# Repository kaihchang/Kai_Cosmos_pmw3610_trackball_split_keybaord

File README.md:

# Kai Cosmos 40, a ZMK split keyboard with pmw3610 trackball

👉 ZMK firmware |
[Dongle-less](https://github.com/kaihchang/zmk-config-kai-cosmos) |
[With Dongle](https://github.com/kaihchang/zmk-config-kai-cosmos-dongle)

Design is mostly created using [rianadon's Cosmos Keyboard Configurator](https://github.com/rianadon/Cosmos-Keyboards). Highly recommend! It's a godsend.

What I did:
1. Scan my own hands with the tools Cosmos Keyboard Configurator provided and my phone's camera.
2. Add a 34mm trackball with [Skree ZMK pmw3610 board](https://github.com/siderakb/pmw3610-pcb) to the right side, which will also be ZMK's main side.
3. Download the models and edit in Blender and Fusion to smooth out the corners.
4. Using the microcontroller template from Cosmos Keyboard Configurator to draw out PCB in Kicad.
5. Implement [badjeff's zmk-pmw3610-driver](https://github.com/badjeff/zmk-pmw3610-driver/tree/main) with some official ZMK settings. Documentations aren't really clear, I recommend searching certain attributes and copying from public repos on Github.
6. Solder, test, change keymap, rinse and repeat.

Things for further improvements:
1. Reset button should be set under MCU holder PCB for easier access.
2. Should have cutouts under MCUs to make built-in LEDs more visible.
3. Should have copper keep out zones beneath MCU's antennae for better Bluetooth signal.
4. Not crucial but important, pmw3610 orientation does matter, since with official settings you can only rotate it in 90-degree increments. Fortunately worked out for me, but I didn't know this beforehand.

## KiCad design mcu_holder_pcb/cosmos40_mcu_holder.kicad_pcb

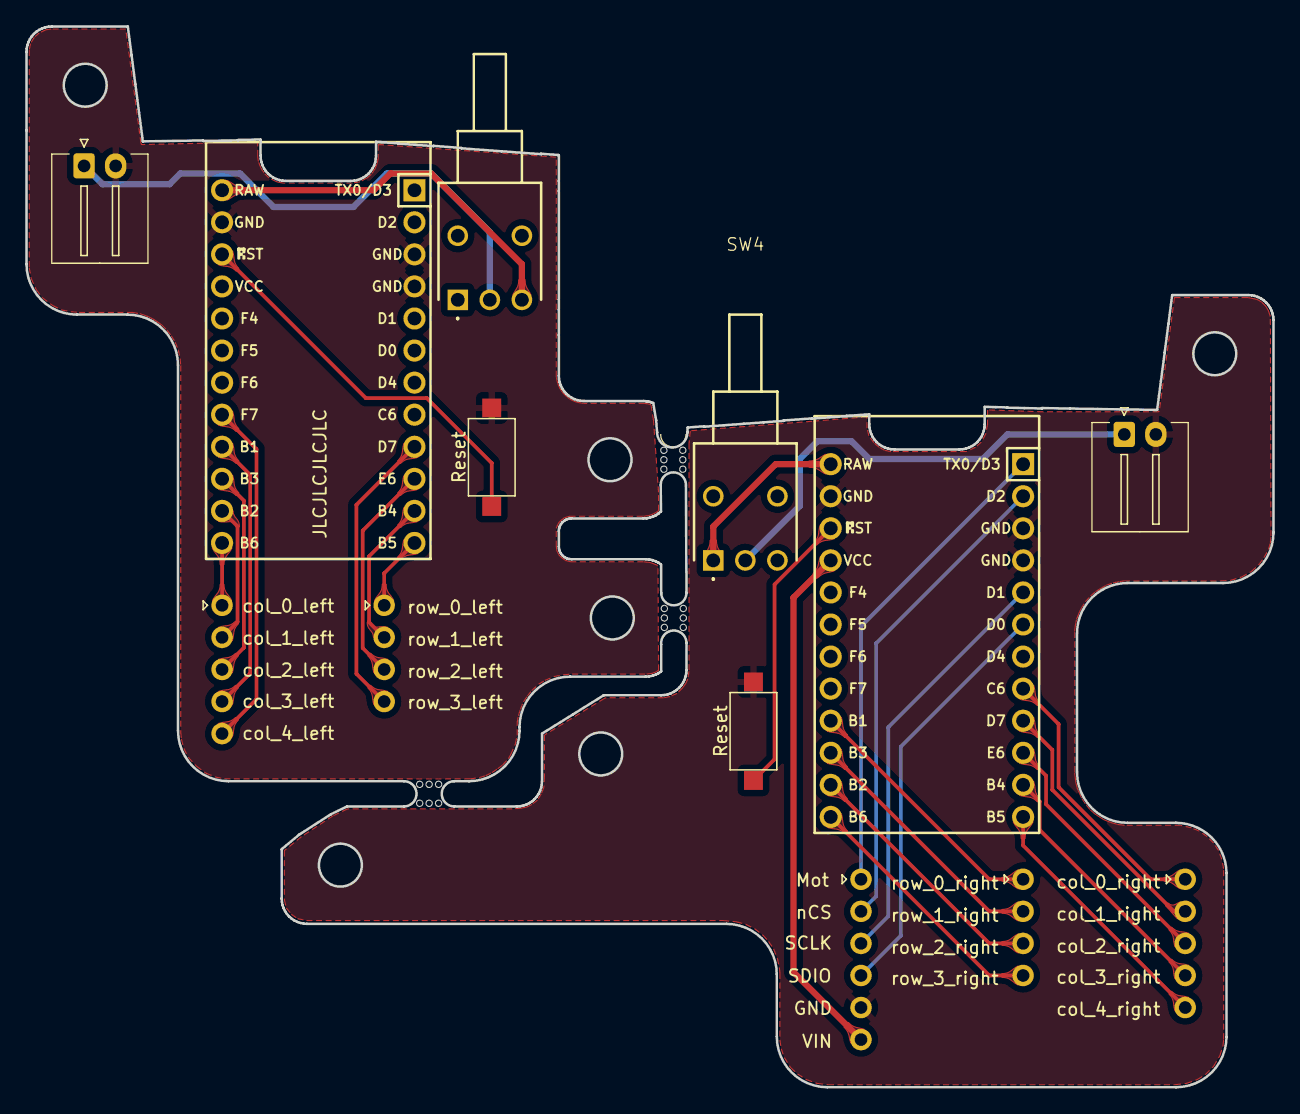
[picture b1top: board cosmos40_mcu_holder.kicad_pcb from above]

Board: 2 copper layers, 98.8 x 84.0 mm, 16 parts (0 on the bottom side), 31 nets.

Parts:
H1, H2, H3: MountingHole_Pad; mouse-bite-2mm-slot
J1: BAT_connector_left; JST_XH_2.54mm_vertical
J2: BAT_connector_right; JST_XH_2.54mm_vertical
J3, J4: Conn_01x04_Socket; PinHeader_1x04_P2.54mm_Vertical
J5, J6: Ribbon; PinHeader_1x05_P2.54mm_Vertical
J7: pmw3610_connector; PinHeader_1x06_P2.54mm_Vertical
Reset: switch_reset_left; SW_SPST_CK_RS282G05A3
Reset#2: switch_reset_right; SW_SPST_CK_RS282G05A3
SW3, SW4: 200AWMSP2T2A1M6RE
U1: nice!nano_flipped_left; Arduino_Pro_Micro_Flipped
U2: nice!nano_flipped_right; Arduino_Pro_Micro_Flipped

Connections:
BAT_left: J1.1, SW3.2 (COM)
BAT_right: J2.1, SW4.2 (COM)
GND_left: J1.2, Reset.2 (B), U1.3 (GND), U1.4 (GND), U1.23 (GND)
GND_right: J2.2, J7.5, Reset#2.2 (B), U2.3 (GND), U2.4 (GND), U2.23 (GND)
Mot: J7.1, U2.1 (TX0/P0.06)
RST_left: Reset.1 (A), U1.22 (RST)
RST_right: Reset#2.1 (A), U2.22 (RST)
SCLK: J7.3, U2.5 (P0.17)
SDIO: J7.4, U2.6 (P0.20)
VIN: J7.6, U2.21 (VCC)
col_0_left: J5.1, U1.13 (NFC1/P0.09)
col_0_right: J6.1, U2.8 (P0.24)
col_1_left: J5.2, U1.14 (NFC2/P0.10)
col_1_right: J6.2, U2.9 (P1.00)
col_2_left: J5.3, U1.15 (P1.11)
col_2_right: J6.3, U2.10 (P0.11)
col_3_left: J5.4, U1.16 (P1.13)
col_3_right: J6.4, U2.11 (P1.04)
col_4_left: J5.5, U1.17 (P1.15)
col_4_right: J6.5, U2.12 (P1.06)
nCS: J7.2, U2.2 (RX1/P0.08)
power_sw_left: SW3.3 (NO), U1.24 (BATIN/P0.04)
power_sw_right: SW4.1 (NC), U2.24 (BATIN/P0.04)
row_0_left: J3.1, U1.12 (P1.06)
row_0_right: J4.1, U2.16 (P1.13)
row_1_left: J3.2, U1.11 (P1.04)
row_1_right: J4.2, U2.15 (P1.11)
row_2_left: J3.3, U1.10 (P0.11)
row_2_right: J4.3, U2.14 (NFC2/P0.10)
row_3_left: J3.4, U1.9 (P1.00)
row_3_right: J4.4, U2.13 (NFC1/P0.09)

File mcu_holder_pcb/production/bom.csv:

Designator,Footprint,Quantity,Value,LCSC Part #
"H1, H2, H3",mouse-bite-2mm-slot,3,MountingHole_Pad,
J1,JST_XH_2.54mm_vertical,1,BAT_connector_left,
J2,JST_XH_2.54mm_vertical,1,BAT_connector_right,
"J3, J4",PinHeader_1x04_P2.54mm_Vertical,2,Conn_01x04_Socket,
"J5, J6",PinHeader_1x05_P2.54mm_Vertical,2,Ribbon,
J7,PinHeader_1x06_P2.54mm_Vertical,1,pmw3610_connector,
RESET_2,SW_SPST_CK_RS282G05A3,1,switch_reset_left,
RESET,SW_SPST_CK_RS282G05A3,1,switch_reset_right,
"SW3, SW4",200AWMSP2T2A1M6RE,2,~,
U1,Arduino_Pro_Micro_Flipped,1,nice!nano_flipped_left,
U2,Arduino_Pro_Micro_Flipped,1,nice!nano_flipped_right,

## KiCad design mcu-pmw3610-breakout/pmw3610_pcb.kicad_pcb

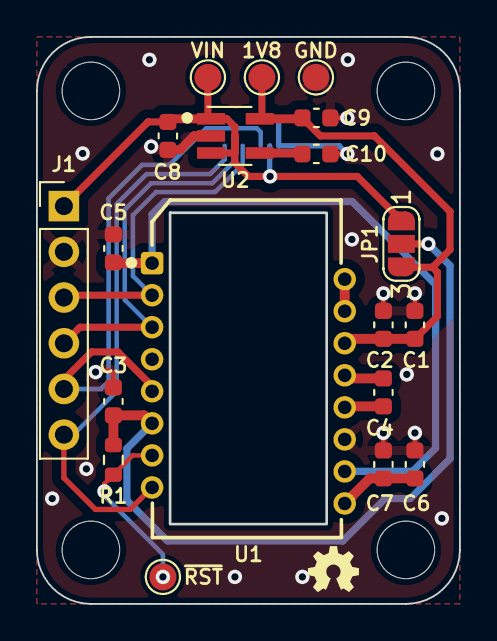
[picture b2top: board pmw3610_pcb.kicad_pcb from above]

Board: 2 copper layers, 23.5 x 31.5 mm, 24 parts (1 on the bottom side), 15 nets.

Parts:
C1: 3.3uF/16V; C_0603_1608Metric
C2, C3: 100nF; C_0603_1608Metric
C4: 100nF X7R; C_0603_1608Metric
C5: 10nF; C_0603_1608Metric
C6: 10uF X7R; C_0603_1608Metric
C7: 10nF X7R; C_0603_1608Metric
C8, C9: 1uF; C_0603_1608Metric
C10: 22nF; C_0603_1608Metric
H1, H2, H3, H4: MountingHole; MountingHole_3.2mm_M3_ISO14580
J1: Conn_01x06; PinHeader_1x06_P2.54mm_Vertical
J2: Conn_01x08; FPC_8P_0.5mm_AFC01-S08FCA-00
JP1: SolderJumper_3_Open; SolderJumper-3_P1.3mm_Open_RoundedPad1.0x1.5mm_NumberLabels
R1: 10k; R_0603_1608Metric
TP1, TP2, TP3, TP4: TestPoint; TestPoint_Pad_D1.5mm
U1: PMW3610; PMW3610DM-SUDU 16Pin
U2: TLV74318PDBVR; SOT-23-5_HandSoldering

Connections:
+1V8: C1.1, C2.1, C9.1, JP1.3 (B), TP3.1, U1.14 (VDD), U2.5 (OUT)
GND: C1.2, C2.2, C3.2, C5.2, C6.2, C7.2, C8.2, C9.2, C10.2, J1.2, J2.1, TP4.1, U1.11 (GND), U2.2 (GND)
MOTION: J1.6, J2.7, U1.8 (MOTION)
unnamed: C5.1, U1.1 (+VCSEL), U1.10 (PASS_T)
unnamed: U1.15 (XYLASER), U1.16 (-VCSEL)
unnamed: C4.2, U1.13 (CN)
unnamed: C4.1, U1.12 (CP)
unnamed: C6.1, C7.1, U1.9 (VCP)
unnamed: C10.1, U2.4 (NC)
SCLK: J1.4, J2.6, U1.3 (SCLK)
SDIO: J1.3, J2.5, U1.2 (SDIO)
VIN: C8.1, J1.1, J2.2, JP1.1 (A), TP2.1, U2.1 (IN), U2.3 (EN)
VIO: C3.1, JP1.2 (C), R1.1, U1.6 (VDDIO)
nCS: J1.5, J2.3, U1.5 (NCS)
nRESET: R1.2, TP1.1, U1.7 (NRESET)

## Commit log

2025-07-19 Update LICENSE
2025-07-19 full file innitial commit
2025-07-19 change files

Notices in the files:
mcu-pmw3610-breakout/pmw3610_pcb.kicad_pcb:
Open Source Hardware, CERN-OHL-P v2
